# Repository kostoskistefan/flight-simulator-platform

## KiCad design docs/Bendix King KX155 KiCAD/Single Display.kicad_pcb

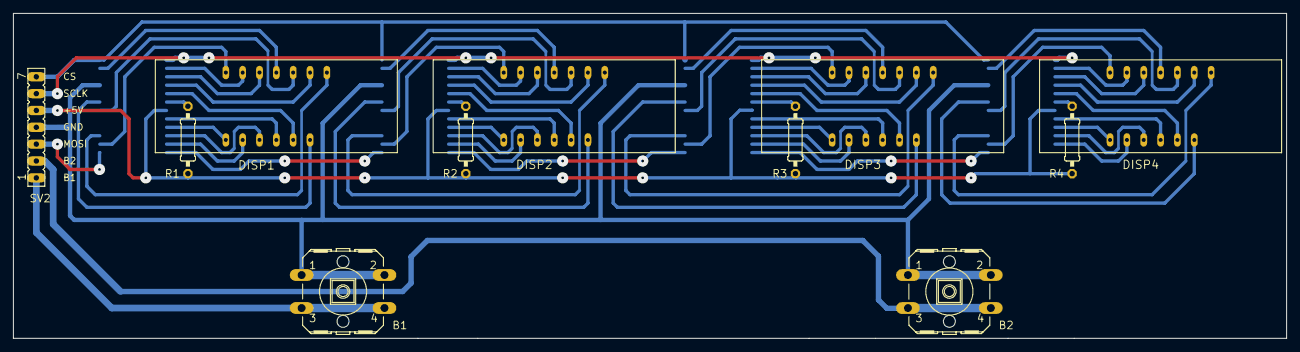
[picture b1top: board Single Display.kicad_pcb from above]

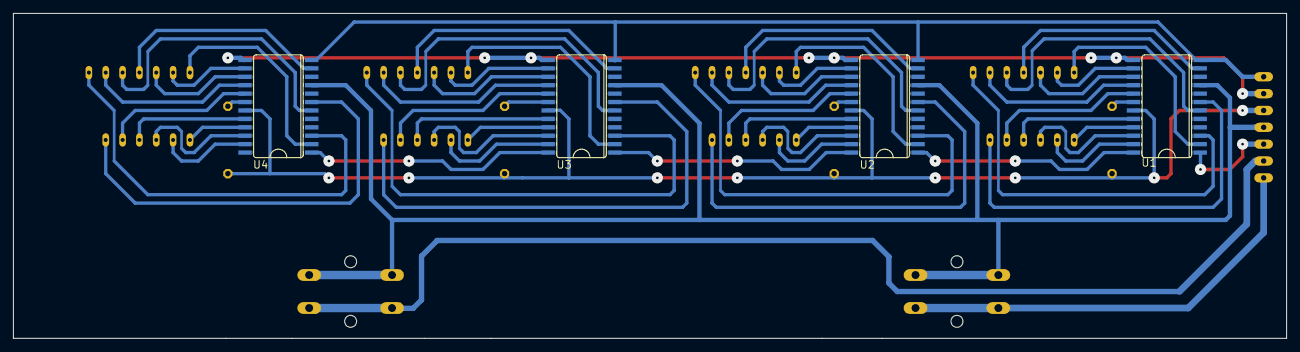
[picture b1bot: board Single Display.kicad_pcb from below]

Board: 2 copper layers, 192.0 x 49.0 mm, 15 parts (4 on the bottom side), 66 nets.

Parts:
B1, B2: 40-XX; B3F-40XX
DISP1, DISP2, DISP3, DISP4: 5_DIGIT_7SEGMENT_DISPLAY
R1, R2, R3, R4: R-EU_0207/10; 0207_10
SV2: FE07-1; FE07
U1, U2, U3, U4: MAX7219CWG; SO24L

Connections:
/CLK: SV2.6, U1.13 (CLK), U2.13 (CLK), U3.13 (CLK), U4.13 (CLK)
/DIN: SV2.3, U1.1 (DIN)
/LOAD: SV2.7, U1.12 (LOAD), U2.12 (LOAD), U3.12 (LOAD), U4.12 (LOAD)
/VCC: R1.1, R2.1, R3.1, R4.1, SV2.5, U1.19 (VCC), U2.19 (VCC), U3.19 (VCC), U4.19 (VCC)
GND: B1.1 (S), B1.2 (S1), B2.1 (S), B2.2 (S1), SV2.4, U1.4 (GND@1), U1.9 (GND@2), U2.4 (GND@1), U2.9 (GND@2), U3.4 (GND@1), U3.9 (GND@2), U4.4 (GND@1), U4.9 (GND@2)
unnamed: B1.3, B1.4 (P1), SV2.1
unnamed: B2.3, B2.4 (P1), SV2.2
unnamed: DISP1.DIG1, U1.2 (DIG0)
unnamed: DISP1.DIG2, U1.11 (DIG1)
unnamed: DISP1.DIG3, U1.6 (DIG2)
unnamed: DISP1.DIG4, U1.7 (DIG3)
unnamed: DISP1.DIG5, U1.3 (DIG4)
unnamed: U1.24 (DOUT), U2.1 (DIN)
unnamed: R1.2, U1.18 (ISET)
unnamed: DISP1.A, U1.14 (SEGA)
unnamed: DISP1.B, U1.16 (SEGB)
unnamed: DISP1.C, U1.20 (SEGC)
unnamed: DISP1.D, U1.23 (SEGD)
unnamed: DISP1.DP, U1.22 (SEGDP)
unnamed: DISP1.E, U1.21 (SEGE)
unnamed: DISP1.F, U1.15 (SEGF)
unnamed: DISP1.G, U1.17 (SEGG)
unnamed: DISP2.DIG1, U2.2 (DIG0)
unnamed: DISP2.DIG2, U2.11 (DIG1)
unnamed: DISP2.DIG3, U2.6 (DIG2)
unnamed: DISP2.DIG4, U2.7 (DIG3)
unnamed: DISP2.DIG5, U2.3 (DIG4)
unnamed: U2.24 (DOUT), U3.1 (DIN)
unnamed: R2.2, U2.18 (ISET)
unnamed: DISP2.A, U2.14 (SEGA)
unnamed: DISP2.B, U2.16 (SEGB)
unnamed: DISP2.C, U2.20 (SEGC)
unnamed: DISP2.D, U2.23 (SEGD)
unnamed: DISP2.DP, U2.22 (SEGDP)
unnamed: DISP2.E, U2.21 (SEGE)
unnamed: DISP2.F, U2.15 (SEGF)
unnamed: DISP2.G, U2.17 (SEGG)
unnamed: DISP3.DIG1, U3.2 (DIG0)
unnamed: DISP3.DIG2, U3.11 (DIG1)
unnamed: DISP3.DIG3, U3.6 (DIG2)
unnamed: DISP3.DIG4, U3.7 (DIG3)
unnamed: DISP3.DIG5, U3.3 (DIG4)
unnamed: U3.24 (DOUT), U4.1 (DIN)
unnamed: R3.2, U3.18 (ISET)
unnamed: DISP3.A, U3.14 (SEGA)
unnamed: DISP3.B, U3.16 (SEGB)
unnamed: DISP3.C, U3.20 (SEGC)
unnamed: DISP3.D, U3.23 (SEGD)
unnamed: DISP3.DP, U3.22 (SEGDP)
unnamed: DISP3.E, U3.21 (SEGE)
unnamed: DISP3.F, U3.15 (SEGF)
unnamed: DISP3.G, U3.17 (SEGG)
unnamed: DISP4.DIG1, U4.2 (DIG0)
unnamed: DISP4.DIG2, U4.11 (DIG1)
unnamed: DISP4.DIG3, U4.6 (DIG2)
unnamed: DISP4.DIG4, U4.7 (DIG3)
unnamed: DISP4.DIG5, U4.3 (DIG4)
unnamed: R4.2, U4.18 (ISET)
unnamed: DISP4.A, U4.14 (SEGA)
unnamed: DISP4.B, U4.16 (SEGB)
unnamed: DISP4.C, U4.20 (SEGC)
unnamed: DISP4.D, U4.23 (SEGD)
unnamed: DISP4.DP, U4.22 (SEGDP)
unnamed: DISP4.E, U4.21 (SEGE)
unnamed: DISP4.F, U4.15 (SEGF)
unnamed: DISP4.G, U4.17 (SEGG)

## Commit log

2023-08-20 Add tft and analog sensors
2023-08-21 Add encoders and radio
2023-09-03 Before final testing
2023-09-05 Fixed x_plane_interface to read multiple values
2023-09-07 Fix calibration
2023-09-12 Remove Serial from code
2023-10-04 Remap pins to use HW SPI
2023-10-06 Add linux starter script for faster SoftAP setup
2023-10-06 Change pins to accommodate updated pcb
2023-10-06 Change X-Plane reply frequency to allow faster hardware reads
2023-10-09 Add waiting for connection and refractor code
2023-11-11 Create LICENSE
2023-11-23 Add hardware design files
